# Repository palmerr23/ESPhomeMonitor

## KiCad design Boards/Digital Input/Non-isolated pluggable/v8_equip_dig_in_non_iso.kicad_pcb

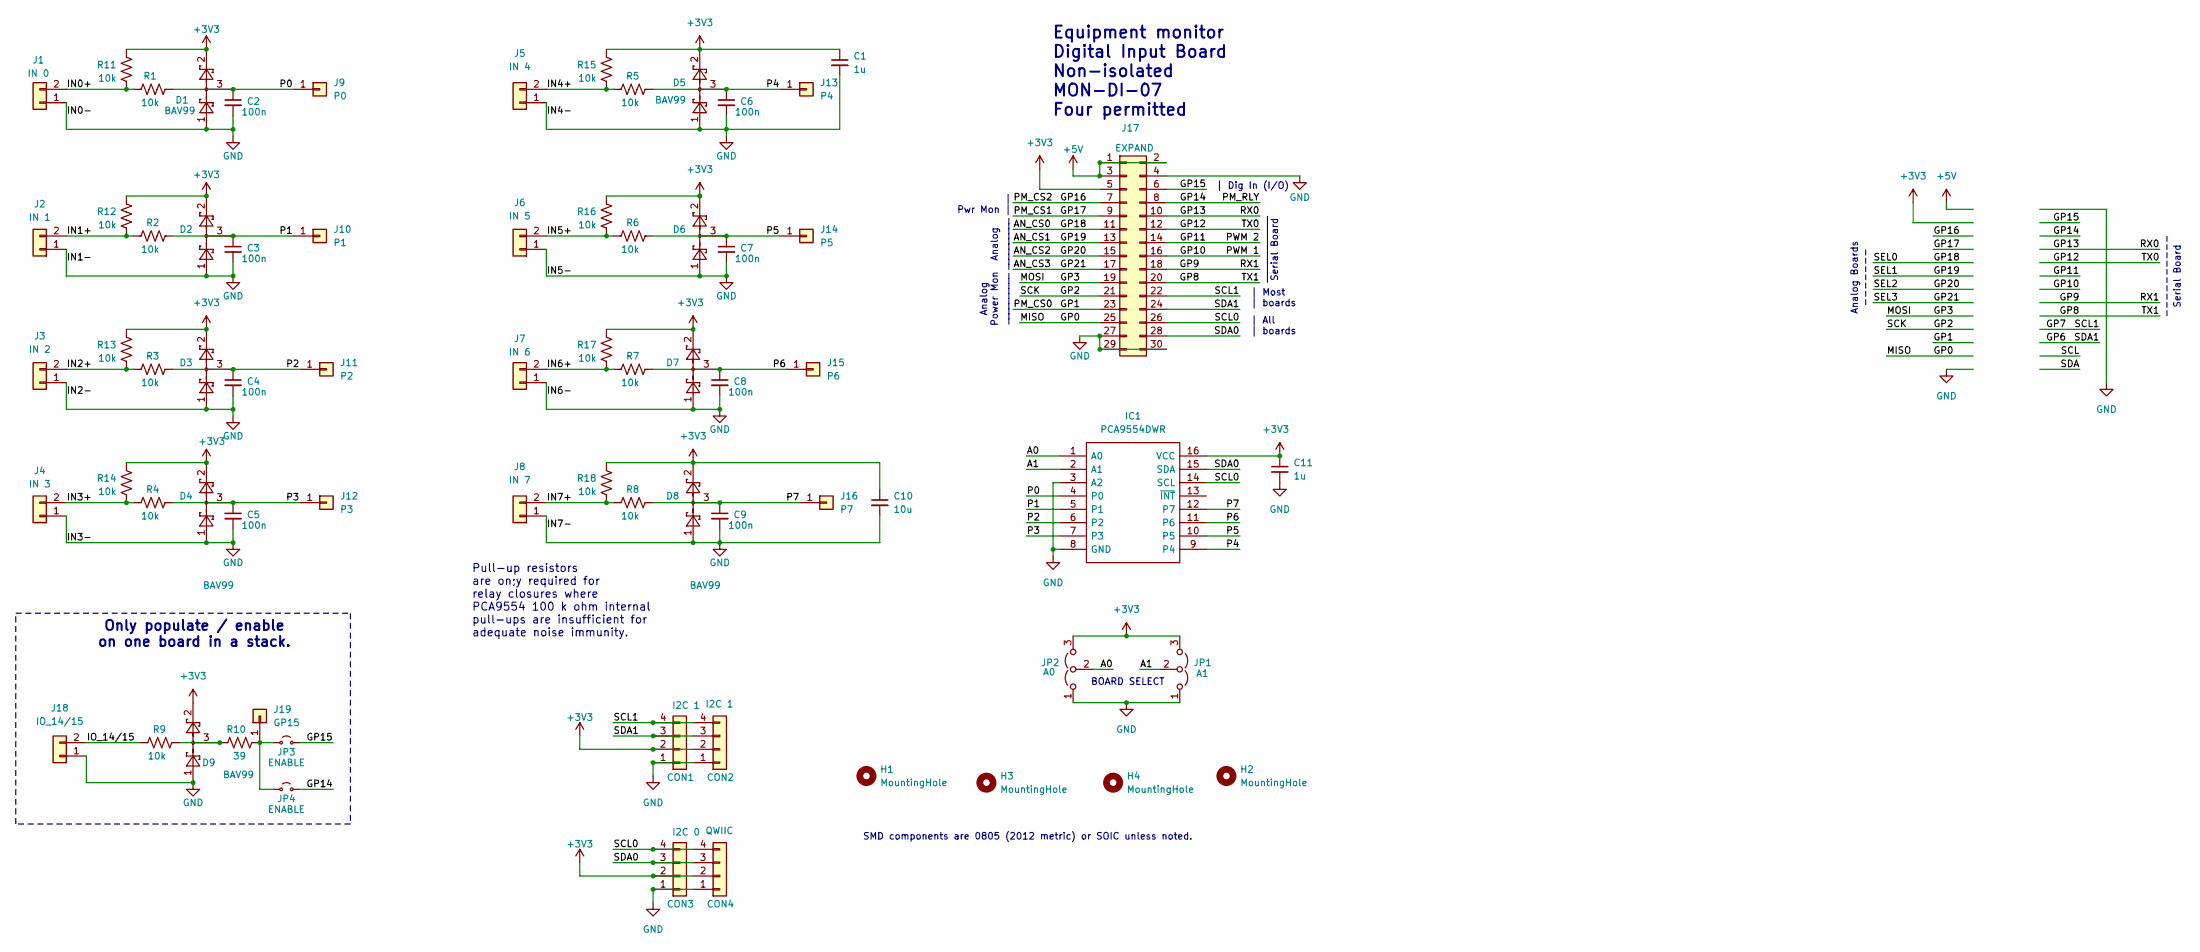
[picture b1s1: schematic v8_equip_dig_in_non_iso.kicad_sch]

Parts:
C1, C11: 1u; C_0805_2012Metric_Pad1.18x1.45mm_HandSolder
C2, C3, C4, C5, C6, C7, C8, C9: 100n; C_0805_2012Metric_Pad1.18x1.45mm_HandSolder
C10: 10u; C_0805_2012Metric_Pad1.18x1.45mm_HandSolder
CON1: I2C 1; PinSocket_1x04_P2.54mm_Vertical
CON2: I2C 1; JST_SH_SM04B-SRSS-TB_1x04-1MP_P1.00mm_Horizontal_wide_MP
CON3: I2C 0; PinSocket_1x04_P2.54mm_Vertical
CON4: QWIIC; JST_SH_SM04B-SRSS-TB_1x04-1MP_P1.00mm_Horizontal_wide_MP
D1, D2, D3, D4, D5, D6, D7, D8, D9: BAV99; SOT-23
H1, H2, H3, H4: MountingHole; MountingHole_3.5mm_no_fill
IC1: PCA9554DWR; SOIC127P1030X265-16N; Mouser Part Number 595-PCA9534DWR
J1: IN 0; K2EDG; Mouser Part Number 649-220110-D021A01LF
J2: IN 1; K2EDG; Mouser Part Number 649-220110-D021A01LF
J3: IN 2; K2EDG; Mouser Part Number 649-220110-D021A01LF
J4: IN 3; K2EDG; Mouser Part Number 649-220110-D021A01LF
J5: IN 4; K2EDG; Mouser Part Number 649-220110-D021A01LF
J6: IN 5; K2EDG; Mouser Part Number 649-220110-D021A01LF
J7: IN 6; K2EDG; Mouser Part Number 649-220110-D021A01LF
J8: IN 7; K2EDG; Mouser Part Number 649-220110-D021A01LF
J9: P0; PinHeader_1x01_P2.54mm_Vertical
J10: P1; PinHeader_1x01_P2.54mm_Vertical
J11: P2; PinHeader_1x01_P2.54mm_Vertical
J12: P3; PinHeader_1x01_P2.54mm_Vertical
J13: P4; PinHeader_1x01_P2.54mm_Vertical
J14: P5; PinHeader_1x01_P2.54mm_Vertical
J15: P6; PinHeader_1x01_P2.54mm_Vertical
J16: P7; PinHeader_1x01_P2.54mm_Vertical
J17: EXPAND; PinHeader_2x15_P2.54mm_Vertical
J18: IO_14/15; PinHeader_1x02_P2.54mm_Vertical; Mouser Part Number 649-220110-D021A01LF
J19: GP15; PinHeader_1x01_P2.54mm_Vertical
JP1: A1; PinHeader_1x03_P2.54mm_Vertical
JP2: A0; PinHeader_1x03_P2.54mm_Vertical
JP3, JP4: ENABLE; SolderJumper-2_P1.3mm_Open_RoundedPad1.0x1.5mm
R1, R2, R3, R4, R5, R6, R7, R8, R9, R11, R12, R13, R14, R15, R16, R17, R18: 10k; R_0805_2012Metric_Pad1.20x1.40mm_HandSolder
R10: 39; R_0805_2012Metric_Pad1.20x1.40mm_HandSolder

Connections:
+3V3: C1.1, C10.1, C11.1, CON1.2, CON2.2, CON3.2, CON4.2, D1.2, D2.2, D3.2, D4.2, D5.2, D6.2, D7.2, D8.2, D9.2, IC1.16 (VCC), J17.5, JP1.3 (B), JP2.3 (B), R11.1, R12.1, R13.1, R14.1, R15.1, R16.1, R17.1, R18.1
+5V: J17.1, J17.2, J17.3
/A0: IC1.1 (A0), JP2.2 (C)
/A1: IC1.2 (A1), JP1.2 (C)
/AN_CS0: J17.11
/AN_CS1: J17.13
/AN_CS2: J17.15
/AN_CS3: J17.17
/GP0: J17.25
/GP1: J17.23
/GP2: J17.21
/GP3: J17.19
/GP6: CON1.3, CON2.3, J17.24
/GP7: CON1.4, CON2.4, J17.22
/GP8: J17.20
/GP9: J17.18
/GP10: J17.16
/GP11: J17.14
/GP12: J17.12
/GP13: J17.10
/GP14: J17.8, JP4.2 (B)
/GP15: J17.6, JP3.2 (B)
/GP16: J17.7
/GP17: J17.9
/IN0+: J1.2, R1.2, R11.2
/IN1+: J2.2, R2.2, R12.2
/IN2+: J3.2, R3.2, R13.2
/IN3+: J4.2, R4.2, R14.2
/IN4+: J5.2, R5.2, R15.2
/IN5+: J6.2, R6.2, R16.2
/IN6+: J7.2, R7.2, R17.2
/IN7+: J8.2, R8.2, R18.2
/IO_14/15: J18.2, R9.2
/P0: C2.1, D1.3, IC1.4 (P0), J9.1, R1.1
/P1: C3.1, D2.3, IC1.5 (P1), J10.1, R2.1
/P2: C4.1, D3.3, IC1.6 (P2), J11.1, R3.1
/P3: C5.1, D4.3, IC1.7 (P3), J12.1, R4.1
/P4: C6.1, D5.3, IC1.9 (P4), J13.1, R5.1
/P5: C7.1, D6.3, IC1.10 (P5), J14.1, R6.1
/P6: C8.1, D7.3, IC1.11 (P6), J15.1, R7.1
/P7: C9.1, D8.3, IC1.12 (P7), J16.1, R8.1
/SCL0: CON3.4, CON4.4, IC1.14 (SCL), J17.26
/SDA0: CON3.3, CON4.3, IC1.15 (SDA), J17.28
GND: C1.2, C2.2, C3.2, C4.2, C5.2, C6.2, C7.2, C8.2, C9.2, C10.2, C11.2, CON1.1, CON2.1, CON3.1, CON4.1, D1.1, D2.1, D3.1, D4.1, D5.1, D6.1, D7.1, D8.1, D9.1, IC1.3 (A2), IC1.8 (GND), J1.1, J2.1, J3.1, J4.1, J5.1, J6.1, J7.1, J8.1, J17.4, J17.27, J17.29, J17.30, J18.1, JP1.1 (A), JP2.1 (A)
unnamed: D9.3, R9.1, R10.2
unnamed: J19.1, JP3.1 (A), JP4.1 (A), R10.1

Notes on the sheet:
| Pwr Mon |
Analog __________
BOARD SELECT
SMD components are 0805 (2012 metric) or SOIC unless noted.
| Dig In (I/O)
Only populate / enable on one board in a stack.
_____________ Serial Board
---------- Serial Board
Equipment monitor Digital Input Board Non-isolated MON-DI-07 Four permitted
Analog Power Mon __________
| All | boards
| Most | boards
Pull-up resistors are on;y required for relay closures where PCA9554 100 k ohm internal pull-ups are insufficient for adequate noise immunity.
Analog Boards -------

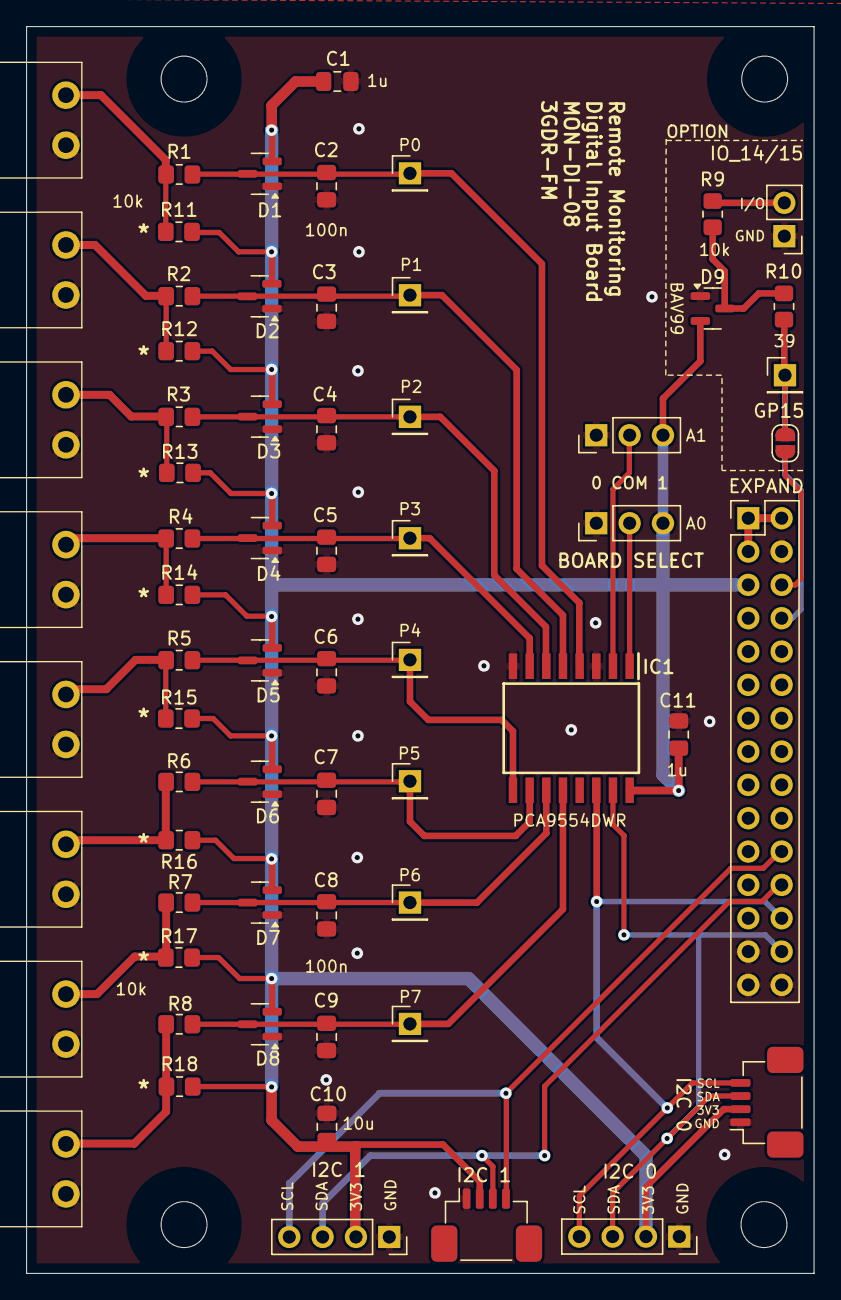
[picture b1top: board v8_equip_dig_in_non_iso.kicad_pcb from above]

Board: 2 copper layers, 60.0 x 95.0 mm, 70 parts (1 on the bottom side), 30 nets.
